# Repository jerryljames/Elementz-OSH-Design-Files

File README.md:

# Elementz Engineers Guild Pvt. Ltd. 

## Elementz-OSH-Design-Files
Open Source Hardware Design Files by Elementz

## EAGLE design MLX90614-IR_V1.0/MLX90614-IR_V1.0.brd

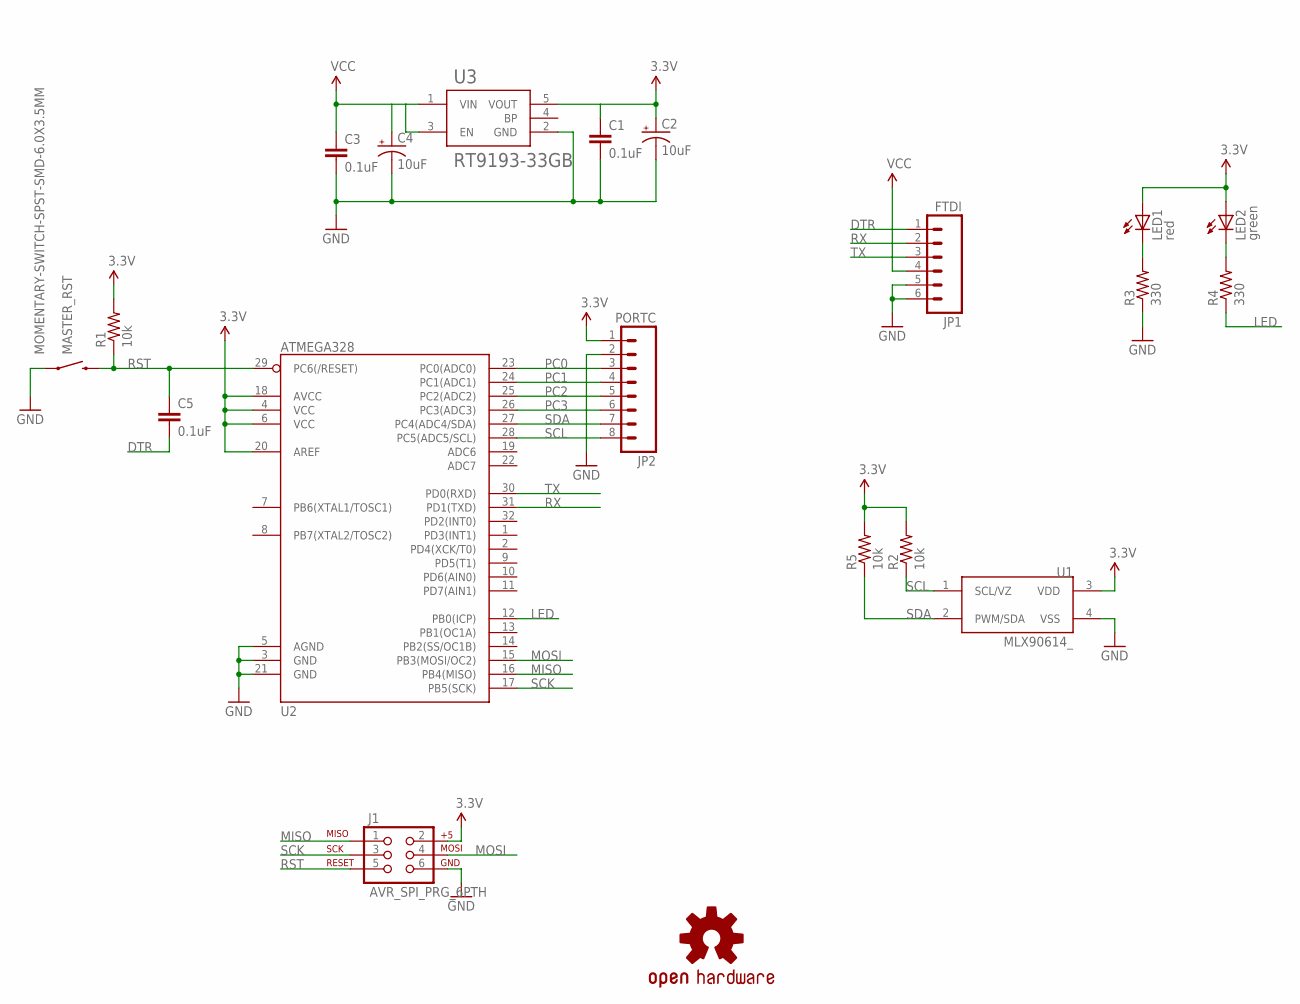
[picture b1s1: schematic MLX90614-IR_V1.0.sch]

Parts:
C1, C3, C5: 0.1uF; 0603-CAP
C2, C4: 10uF; EIA3216
J1: AVR_SPI_PRG_6PTH; 2X3
JP1: FTDI; 1X06
JP2: PORTC; 1X08
LED1: red; LED-0603
LED2: green; LED-0603
MASTER_RST: MOMENTARY-SWITCH-SPST-SMD-6.0X3.5MM; TACTILE_SWITCH_SMD_6.0X3.5MM
R1, R2, R5: 10k; 0603-RES
R3, R4: 330; 0603-RES
U1: MLX90614_; TO-39
U2: ATMEGA328; TQFP32-08
U3: RT9193-33GB; SOT94P279X129-5N
U$1: OSHW-LOGOS; OSHW-LOGO-S

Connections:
3.3V: C1.1, C2.A (+), J1.2, JP2.1, LED1.A, LED2.A, R1.2, R2.2, R5.2, U1.3 (VDD), U2.4 (VCC), U2.6 (VCC), U2.18 (AVCC), U2.20 (AREF), U3.5 (VOUT)
DTR: C5.2, JP1.1
GND: C1.2, C2.C (-), C3.2, C4.C (-), J1.6, JP1.5, JP1.6, JP2.2, MASTER_RST.1, R3.1, U1.4 (VSS), U2.3 (GND), U2.5 (AGND), U2.21 (GND), U3.2 (GND)
LED: R4.1, U2.12 (PB0(ICP))
MISO: J1.1, U2.16 (PB4(MISO))
MOSI: J1.4, U2.15 (PB3(MOSI/OC2))
unnamed: LED1.C, R3.2
unnamed: LED2.C, R4.2
PC0: JP2.3, U2.23 (PC0(ADC0))
PC1: JP2.4, U2.24 (PC1(ADC1))
PC2: JP2.5, U2.25 (PC2(ADC2))
PC3: JP2.6, U2.26 (PC3(ADC3))
RST: C5.1, J1.5, MASTER_RST.2, R1.1, U2.29 (PC6(/RESET))
RX: JP1.2, U2.31 (PD1(TXD))
SCK: J1.3, U2.17 (PB5(SCK))
SCL: JP2.8, R2.1, U1.1 (SCL/VZ), U2.28 (PC5(ADC5/SCL))
SDA: JP2.7, R5.1, U1.2 (PWM/SDA), U2.27 (PC4(ADC4/SDA))
TX: JP1.3, U2.30 (PD0(RXD))
VCC: C3.1, C4.A (+), JP1.4, U3.1 (VIN), U3.3 (EN)

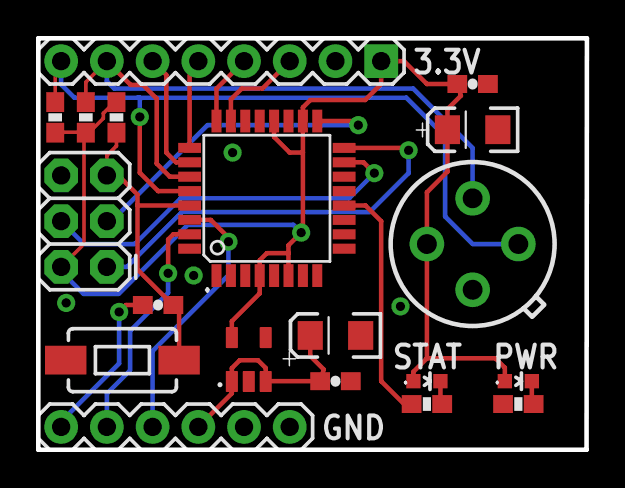
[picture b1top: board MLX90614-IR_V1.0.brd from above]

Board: 2 copper layers, 30.5 x 22.9 mm, 20 parts (1 on the bottom side), 19 nets.

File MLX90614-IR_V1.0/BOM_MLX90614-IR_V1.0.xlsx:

Part | Value | Device | Package | Description | MF | MPN | OC_FARNELL | PROD_ID | SF_SKU
C1 | 0.1uF | CAP0603-CAP | 0603-CAP | Capacitor
C2 | 10uF | CAP_POL1206 | EIA3216 | Capacitor Polarized
C3 | 0.1uF | CAP0603-CAP | 0603-CAP | Capacitor
C4 | 10uF | CAP_POL1206 | EIA3216 | Capacitor Polarized
C5 | 0.1uF | CAP0603-CAP | 0603-CAP | Capacitor
J1 | AVR_SPI_PRG_6PTH | AVR_SPI_PRG_6PTH | 2X3 | AVR ISP 6 Pin
JP1 | FTDI | M06SIP | 1X06 | Header 6
JP2 | PORTC | M08 | 1X08 | Header 8
LED1 | red | LED0603 | LED-0603 | LEDs
LED2 | green | LED0603 | LED-0603 | LEDs
MASTER_RST | MOMENTARY-SWITCH-SPST-SMD-6.0X3.5MM | MOMENTARY-SWITCH-SPST-SMD-6.0X3.5MM | TACTILE_SWITCH_SMD_6.0X3.5MM | Momentary Switch (Pushbutton) - SPST |  |  | unknown | SWCH-00815 | COM-08229
R1 | 10k | RESISTOR0603-RES | 0603-RES | Resistor
R2 | 10k | RESISTOR0603-RES | 0603-RES | Resistor
R3 | 330 | RESISTOR0603-RES | 0603-RES | Resistor
R4 | 330 | RESISTOR0603-RES | 0603-RES | Resistor
R5 | 10k | RESISTOR0603-RES | 0603-RES | Resistor
U1 | MLX90614_ | MLX90614_ | TO-39 | Melexis IR Thermometer
U2 | ATMEGA328P | ATMEGA328P-AU | TQFP32
U3 | RT9193-33GB | RT9193-33GB | SOT23-5 | Linear Voltage Regulator IC 1 Output 300mA

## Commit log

2020-10-02 IR Sensor Module 555 V1.0
2020-10-02 L298N Motor Driver V1.0
2020-10-02 MLX90614 IR V1.0
2020-10-02 IRF520 MOSFET Driver V1.0
2020-10-02 MQxx Gas Sensor V1.0
2020-10-02 IR Sensor Module V1.0
2020-10-09 3 Color(RGB)LED Module V1.0 added
2020-11-24 Added DIP 3 Color LED Module Schematic in pdf
2020-11-24 DIP LED Module V1.0
2020-11-24 LDR Module V1.0
2020-11-24 Potentiometer Module V1.0
2020-11-24 Buzzer Module V1.0
2020-11-24 IR_Sensor_Module_555_V1.1
    Trace width & via diameter increased
2020-11-24 IR_Sensor_Module_555_V1.0_B
    Single Layer version of IR 555 with Through hole components
2020-11-24 AMS1117 5V/3.3V Step-Down Power Supply Module
2020-11-24 DC-DC 12V to 3.3V 5V Multi Output Voltage Conversion V1.0

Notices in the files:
parts and their libraries:
SparkFun-Switches: Licensing: Creative Commons ShareAlike 4.0 International - https://creativecommons.org/licenses/by-sa/4.0
